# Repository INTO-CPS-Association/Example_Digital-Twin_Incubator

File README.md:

# Example Digital Twin: The Incubator

This is a case study of an Incubator with the purpose of understanding the steps and processes involved in developing a digital twin system.
This incubator is an insulated container with the ability to keep a temperature and heat, but not cool.

To understand what a digital twin is, we recommend you read/watch one or more of the following resources:
- Feng, Hao, Cláudio Gomes, Casper Thule, Kenneth Lausdahl, Alexandros Iosifidis, and Peter Gorm Larsen. “Introduction to Digital Twin Engineering.” In 2021 Annual Modeling and Simulation Conference (ANNSIM), 1–12. Fairfax, VA, USA: IEEE, 2021. https://doi.org/10.23919/ANNSIM52504.2021.9552135.
- [Claudio's presentation at Aarhus IT](https://videos.ida.dk/media/Introduction+to+Digital+Twin+Engineering+with+Cl%C3%A1udio+%C3%82ngelo+Gon%C3%A7alves+Gomes%2C+Aarhus+Universitet/1_7r1j05g8/256930613)

# Contents
- [Example Digital Twin: The Incubator](#example-digital-twin-the-incubator)
- [Contents](#contents)
- [About this Document](#about-this-document)
- [Overview of the Documentation](#overview-of-the-documentation)
   - [Searching](#searching)
- [Terminology](#terminology)
- [Our Concept of Digital Twin](#our-concept-of-digital-twin)
- [The Incubator Physical Twin](#the-incubator-physical-twin)
   - [Hardware Overview](#hardware-overview)
      - [Raspberry Pi GPIO connections](#raspberry-pi-gpio-connections)
      - [Temperature Sensor Mapping](#temperature-sensor-mapping)
      - [Connecting to the Raspberry PI](#connecting-to-the-raspberry-pi)
   - [CAD Model](#cad-model)
   - [Dynamic Models](#dynamic-models)
   - [Running The Incubator Physical Twin](#running-the-incubator-physical-twin)
- [The Digital Twin](#the-digital-twin)
   - [System Architecture](#system-architecture)
      - [Self-Adaptation](#self-adaptation)
   - [Datasets and Experiment Reports](#datasets-and-experiment-reports)
   - [Running the Digital Twin](#running-the-digital-twin)
      - [First-time Setup](#first-time-setup)
      - [After First-time Setup: Starting the DT Framework](#after-first-time-setup-starting-the-dt-framework)
      - [Running Unit Tests](#running-unit-tests)
      - [Running Integration Tests](#running-integration-tests)
- [Start visualization](#start-visualization)
- [Command Line Utilities to Interact with DT](#command-line-utilities-to-interact-with-dt)
   - [Mess With Lid Script](#mess-with-lid-script)
- [Diagnosing Startup Errors](#diagnosing-startup-errors)
   - [RabbitMQ Setup](#rabbitmq-setup)
   - [InfluxDB Setup](#influxdb-setup)
      - [First time configuration of InfluxDB server](#first-time-configuration-of-influxdb-server)
      - [Start InfluxDB server](#start-influxdb-server)
      - [Management of Influxdb](#management-of-influxdb)
      - [Initial Setup of Database](#initial-setup-of-database)
      - [Common Errors](#common-errors)
         - [Unauthorized API access](#unauthorized-api-access)
- [Repository Maintenance Instructions](#repository-maintenance-instructions)
   - [Code Organization](#code-organization)
# About this Document

**Goal:** The goal of this document is to provide users with a basic overview of the digital twin incubator and enabled them to run it on their computers.

**Audience:** This documentation is targeted at users who are acquainted with running programs from the command line and are able to install [python](https://www.python.org/) and run python scripts.

# Overview of the Documentation

The documentation is all contained into a single document for simplicity and ease of maintenance.
If the user wishes to see the documentation in some other format then we recommend cloning this repository and using [Pandoc](https://pandoc.org/) to convert the documentation into another format.

## Searching

Searching the documentation can be done by using the browser search function or using Github's search feature on top of the screen.

# Terminology

- **Plant** -- we use the term in the traditional control systems sense. The plant refers to the box contents, the heater, the sensor, and the fan. Basically it is the stuff that the controller is sensing and actuating on.
- **Controller** -- To control this responsibility is to decide when to turn on/off the heater.
- **Low Level Driver** --- This refers to the component that decouples the controller from the plant. It forms a layer that abstracts away from the details of how the actuators and sensors work and enables us to run the whole system locally on a computer without the need to connect to a real plant.

# Our Concept of Digital Twin

A digital twin is a software system that supports the operation of a cps (called the physical twin).
So the following documentation describes the physical twin first and then the digital twin.

# The Incubator Physical Twin

The overall purpose of the system is to reach a certain temperature within a box and keep the temperature regardless of content.

The system consists of:
- 1x Styrofoam box in order to have an insulated container
- 1x heat source to heat up the content within the Styrofoam box.
- 1x fan to distribute the heating within the box
- 2x temperature sensor to monitor the temperature within the box
- 1x temperature Sensor to monitor the temperature outside the box
- 1x controller to actuate the heat source and the fan and read sensory information from the temperature sensors, and communicate with the digital twin.

## Hardware Overview
Hardware Elements
- 3 temperature sensors of the type DS18S20
- 1 heat bed of the type RepRap PCB Heat bed MK2a (improved design)
  - Dimensions (Heat Bed): 200mm x 200mm
  - Resistance: 0.9 - 1.1 Ohms 
  - Operating voltage: 12 Volts
  - Operating current: 11 - 13 Amps
- 1 Fan 24V 92x25 B 87,4m³/h 34dBA - https://elektronik-lavpris.dk/files/sup2/EE92252B1-A99_D09023340G-00.pdf - https://elektronik-lavpris.dk/p122514/ee92252b1-a99-fan-24v-92x25-b-874m-h-34dba/
- Raspberry Pie starter kit
  - Raspberry Pi 4 Model B - 4 GB - https://www.raspberrypi.org/documentation/hardware/raspberrypi/bcm2711/rpi_DATA_2711_1p0_preliminary.pdf
  - 6GB Micro SD - Class A1 - Med NOOBS
  - Officiel Raspberry Pi USB-C Strømforsyning – EU – 5V 3A - Sort
  - Officiel Raspberry Pi 7" Touchscreen Display
  - SmartiPi Touch 2 - Case til Raspberry Pi 7" Touchscreen Display 
  - USB Micro SD Kortlæser
- Thermo box - Climapor thermokasse m/låg t/Eurokasse 54,5x35x18 cm
- Custom Printed Circuit Board Electronics. You can find more information [here](./software/docs/electronics/doc/doc.pdf).

### Raspberry Pi GPIO connections
- GPIO 12: PWM Heater 
- GPIO 13: PWM Fan
- GPIO 4: 1-wire temperature sensors

### Temperature Sensor Mapping
In order to read a temperature from the temperature sensors multiple IDs can be found in `/sys/bus/w1/devices/`.

If they are not visible there, check that the wires are well connected. Also check whether that the kernel submodules are active:
```bash
pi@incubatorpi:~/source/software $ lsmod | grep w1
w1_therm               28672  0
w1_gpio                16384  0
wire                   36864  2 w1_gpio,w1_therm
```

So to read a value from a sensor, one can do: `cat /sys/bus/w1/devices/10-0008039ad4ee/w1_slave`.

The sensors were connected according to [this online guide](https://www.circuitbasics.com/raspberry-pi-ds18b20-temperature-sensor-tutorial/).

Each ID in the `/sys/bus/w1/devices` folder correspond to a particular sensor. Follow the wires of the temperature sensors, and you will find a paper label with a number on it.
The ID to number mapping is:

ID to Sensor Number Mapping:

| ID              | Sensor Number |
|-----------------|:-------------:|
| 10-0008039ad4ee |       1       |
| 10-0008039b25c1 |       2       |
| 10-0008039a977a |       3       |

### Connecting to the Raspberry PI

The simplest is to just connect a keyboard, screen, and mouse to the pi, then use setup a hotspot with your phone, and connect the PI to it. Ensure that the rabbitmq server is accessible from the PI, and you should be able to run everything. We do not recommend running the influxdb within the PI itself. To gather data on the pi, we recommend [start_csv_data_recorder](software/startup/start_csv_data_recorder.py), which will store locally a set of csv files with the data from the [low_level_driver_server.py](software/incubator/physical_twin/low_level_driver_server.py). On another computer that has access to the rabbitmq server and influxdb server, you can run the [start_influx_data_recorder.py](software/startup/start_influx_data_recorder.py) to forward the data to the influxdb server.

You can SSH to the PI. The username and password is physically located on the Pi.

## CAD Model

A .obj file is available at: [figures/incubator_plant.obj](figures/incubator_plant.obj).

Ongoing development of the cad model is at 
[incubator](https://www.tinkercad.com/things/ls1YolyX1fc-incubatorv20230429)

## Dynamic Models

Most models are implemented using the [oomodellingpython](https://gitlab.au.dk/clagms/oomodellingpython/) package.

Models can be organized as plant models, [controller models](software/incubator/models/controller_models), or physical twin models (the later couple plant and controller together):
- Controller Models: we have implemented multiple controller models but only document the following:
  - [controller_model4](software/incubator/models/controller_models/controller_model4.py) -- This is like a [bang bang controller](https://en.wikipedia.org/wiki/Bang%E2%80%93bang_control) which tries to keep the temperature within an upper and lower bound.
- Plant Models: we have implemented multiple plant models but document the following:
  - [four_parameter_model](software/incubator/models/plant_models/four_parameters_model/four_parameter_model.py) --- this model represents the average temperature dynamics inside the box considering both the heater and the air as heat accumulating entities.
- [Physical Twin Models](software/incubator/models/physical_twin_models):
  -  [system_model4](software/incubator/models/physical_twin_models/system_model4.py) --- this model couples the controller_model4 model and the four_parameter_model.

## Running The Incubator Physical Twin

On the raspberry pi: 
1. Start the [low_level_driver_server.py](software/incubator/physical_twin/low_level_driver_server.py)
   ```powershell 
   PS software> python -m incubator.physical_twin.low_level_driver_server
   ```
2. Start the controller you wish to use. For example the [start_controller_physical.py](software/startup/start_controller_physical.py) is:
   ```powershell 
   PS software> python -m startup.start_controller_physical
   ```

# The Digital Twin

The DT follows a service based architecture, with different services communicating with each other via a [RabbitMQ message exchange](https://www.rabbitmq.com/) running on a [docker](https://www.docker.com/products/docker-desktop) container.
Each service is started with a python script, and most services refer to [software/startup.conf](software/startup.conf) for their configuration.

The code that starts the services is in [software/startup](software/startup).
It is possible to start all services (except the 3D visualization service) from the same script [software/startup/start_all_services.py](software/startup/start_all_services.py) or each service individually.

The services (and their starting scripts) currently implemented are:
- [incubator_realtime_mockup](software/startup/start_incubator_realtime_mockup.py) -- implements a real time plant simulation mockup so that the whole digital twin system can be run locally on any computer without the need to connect to an external physical twin. When using a real physical twin this service is not started.
- [low_level_driver_mockup](software/startup/start_low_level_driver_mockup.py) -- This instantiates a low level driver service that is wired to work with a real time plant simulator mockup. When using a real physical twin this service is not started.
- [influx_data_recorder](software/startup/start_influx_data_recorder.py) -- the service listens to a particular topic from RabbitMQ records the messages into the time series database [InfluxDB](https://portal.influxdata.com/downloads/)
- [plant_kalmanfilter](software/startup/start_plant_kalmanfilter.py) -- This service estimates the full state of the system and is used as a basis for anomaly detection.
- [plant_simulator](software/startup/start_plant_simulator.py) -- The service can run simulations based on the data from the time series database with different conditions for the plant model.
- [simulator](software/startup/start_simulator.py) -- This service can run simulations of the controller and plant system from data based on the data from the time series databases with different conditions.
- [calibrator](software/startup/start_calibrator.py) -- The service can use data from the time series database to estimate the parameters of the plant model.
- [controller_physical](software/startup/start_controller_physical.py) -- this service implements the controller.
- [supervisor](software/startup/start_supervisor.py) -- This service can periodically retune the controller.
- [self_adaptation_manager](software/startup/start_self_adaptation_manager.py) -- the service implements the self-adaptation which checks whether the physical characteristics of the plant have changed and can trigger a recalibration as well as controller tuning when that happens.
- [3d_visualization](software/digital_twin/visualization/project.godot) -- This service is a [Godot](https://godotengine.org/) project that shows a 3D rendering of the incubator. 
- [energy_saver](software/startup/start_energy_saver.py) -- This service is a simplified version of [self_adaptation_manager](software/startup/start_self_adaptation_manager.py) that reconfigures the controller to a lower energy consumption configuration when the lid is open.

## System Architecture

We use the [C4 Model](https://c4model.com/) to document the software architecture.

All communication goes through the RabbitMQ server, even the communication between the Controller and Plant.
The Controller communicates with the Plant by listening and sending RabbitMQ messages to the [low_level_driver_server.py](./software/incubator/physical_twin/low_level_driver_server.py).

Anyone else interested in this communication, such as the digital twin, can listen to it as well.

### Self-Adaptation

The most complex behavior is the self-adaptation, as it involves most implemented DT components.

This is introduced in the following paper, which we recommend you read:
- Feng, Hao, Cláudio Gomes, Santiago Gil, Peter H. Mikkelsen, Daniella Tola, Peter Gorm Larsen, and Michael Sandberg. “Integration Of The Mape-K Loop In Digital Twins.” In 2022 Annual Modeling and Simulation Conference (ANNSIM), 102–13. San Diego, CA, USA: IEEE, 2022. https://doi.org/10.23919/ANNSIM55834.2022.9859489.
- *Note that diagrams in the paper are likely outdated. Updated diagrams are shown below*

The main components and their dependencies are:

Legend:
- [MQ] - Communication happens via RabbitMQ messages.
- [API] - Communication happens via method call.

The following shows the main stages involved in a self-adaptation:

In particular, these are followed by the SelfAdaptationManager:

The following diagram shows the main interactions between the main entities that participate in the self-adaptation process. It is assumed that an anomaly has occurred due to the lid being open.

## Datasets and Experiment Reports

See [incubator/datasets](./software/incubator/datasets/README.md)

## Running the Digital Twin

It is possible to run the digital twin on our computer, with or without a connection to the physical twin.

*You're advised to read carefully all documentation before acting on any instruction.*

### First-time Setup
1. Open terminal in [software](software).
2. (Optional) Create a virtual environment: `python -m venv venv`
3. (Optional) Activate the virtual environment (there are multiple possible activate scripts. Pick the one for your terminal.): 
   1. Windows Powershell:`.\venv\Scripts\Activate.ps1` 
   2. Linux/Mac: `source venv/bin/activate`
4. (Optional) Install pip wheel: `pip install wheel`
5. Install dependencies:
   1. `pip install -r ./requirements.txt`
6. Install [docker](https://www.docker.com/products/docker-desktop) (see [Docker Homepage](https://docs.docker.com/desktop/))
   1. On Linux, also install the [Docker compose plugin](https://docs.docker.com/compose/install/linux/)
8. (Optional) Install [Godot](https://godotengine.org/) in case you want to load a 3D visualization. 

### After First-time Setup: Starting the DT Framework

1. Inspect the [startup.conf](./software/startup.conf) in this folder. You should not need to change anything for running the DT locally.
2. Make sure docker is running. 
3. Run
   ```bash
   software$ python -m startup.start_all_services
   ```
4. After starting all services successfully, the controller service will start producing output that looks like the following:
   ````
   time           execution_interval  elapsed  heater_on  fan_on   room   box_air_temperature  state 
   19/11 16:17:59  3.00                0.01     True       False   10.70  19.68                Heating
   19/11 16:18:02  3.00                0.03     True       True    10.70  19.57                Heating
   19/11 16:18:05  3.00                0.01     True       True    10.70  19.57                Heating
   19/11 16:18:08  3.00                0.01     True       True    10.69  19.47                Heating
   19/11 16:18:11  3.00                0.01     True       True    10.69  19.41                Heating
   ````
5. Login to http://localhost:8086/ (or more generally http://[Influxdb_IP]:8086/) to see the influxdb management page, were you can create dashboards to see the data produced by the incubator. The login details are:
   - user=`incubator`
   - password=`incubator`
6. Login http://localhost:15672/ to see the RabbitMQ management page. The login details are:
   - user=`incubator`
   - password=`incubator`
7. Optional: [Start visualization](#start-visualization)
8. See [Diagnosing Startup Errors](#diagnosing-startup-errors) in case you encounter problems
9. Recommended: [Run the unit tests](#running-unit-tests)
10. Recommended: [Run the integration tests](#running-integration-tests)

### Running Unit Tests

Make sure you can successfully [start the DT framework](#after-first-time-setup-starting-the-dt-framework)

To run the unit tests, open a terminal in [software](software), and
1. Activate virtual environment
2. If using powershell, run [./run_tests.ps1](./software/run_tests.ps1)
3. Otherwise:
   1. Set environment variable `CLIMODE = "ON"`
   2. Run tests: `python -m unittest discover -v incubator/tests -p "*.py"`

### Running Integration Tests

Make sure you can successfully [start the DT framework](#after-first-time-setup-starting-the-dt-framework) and [run the unit tests](#running-unit-tests) before attempting to run the integration tests.

The script [run_integration_tests.ps1](./software/run_integration_tests.ps1) contains the instructions.

# Start visualization

We assume the reader is broadly familiar with [Godot](https://godotengine.org/) engine.

1. Download and install [Godot Engine - .NET v4.1.1](https://godotengine.org/download/archive/4.1.1-stable/). 
   * Note that it must be the .NET version.
   * You may also need to install the [.NET SDK](https://dotnet.microsoft.com/en-us/download)
2. Open [project.godot](software/digital_twin/visualization/project.godot) with Godot engine.
3. The UI should look like:
   
4. Make sure the RabbitMQ server is running.
5. Build and run the project by clicking on the "play" button in the top-right corner (or press F5). 
   1. If the application crashes when opening the project, it could be due to:
      1. Connection from Godot to Rabbitmq server failed (check the Errors tab in Godot UI).
      2. You GPU does not support the Vulkan rendering API. Open a terminal and run the following command: 
      ```
      C:\path\to\your\godot4.exe --rendering-driver opengl3.
      ```
6. In the connection menu, add the connection configuration parameters that are in the [startup.conf](software/startup.conf). The result should look like this:
   
7. Press connect and then start. It will look like this:

# Command Line Utilities to Interact with DT
The Incubator contains several scripts for interacting with the DT as it is running live. The scripts can be found in [software/cli](software/cli).
The scripts can be executed by following the pattern: `python -m cli.<script_name>`.<br>
For instance, to generate dummy data the following script can be executed: `python -m cli.generate_dummy_data`. Notice that some scripts require extra parameters.

## Mess With Lid Script
Certain configurations of the Incubator support anomaly detection to determine if the styrofoam lid has been removed from the box.<br>
When running a mocked version of the PT, the behavior of removing the lid can be simulated through the [software/cli/mess_with_lid_mock.py](software/cli/mess_with_lid_mock.py) script.<br>
In practice, the simulation is accomplished by changing the $G_{box}$ parameter of the mocked PT. The $G_{box}$ represents the rate of energy transfer between the air inside the box and the air outside the box.

**Executing the script:**<br>
The script can be executed by running `python -m cli.mess_with_lid_mock <N>`, where $N$ represents a positive integer to multiply the original $G_{box}$ with.<br>
For instance, the `python -m cli.mess_with_lid_mock 100` simulates a greater loss of energy to the outside (lid off) and `python -m cli.mess_with_lid_mock 1` simulates the original behavior (lid on).

# Diagnosing Startup Errors

If any errors show up during the startup process, check that the RabbitMQ server and InfluxDB are being correctly started. 

The following instructions were used to configure these services in the first time and may help you test them:

## RabbitMQ Setup

To start the RabbitMQ server, run the following in [software/incubator/communication/installation](software/incubator/communication/installation):
``` Powershell
# start and install rabbitmq container
PS software\incubator\communication\installation> docker-compose up --detach --build
[MACOS: docker compose up --detach --build]

# Check logs of rabbitmq-server
PS software\incubator\communication\installation> docker logs rabbitmq-server

# Run script to test server (assumes you have correct environment)
cd [RepoRoot]\software\
[Activate virtual environment]
PS software> python -m incubator.communication.installation.test_server

# Stop and remove the server
PS software> docker-compose down -v
[MACOS: docker compose down -v]
```

The script should produce:
```
Sending message...
Message sent.
Retrieving message. Received message is {'text': '321'}
```

More information about the [Dockerfile](software/incubator/communication/installation/Dockerfile):
https://hub.docker.com/_/rabbitmq

Management of local RabbitMQ:
1. Start RabbitMQ server
2. Open http://localhost:15672/ on your browser.
3. User and pass configuration are stored in [rabbitmq.conf](software/incubator/communication/installation/rabbitmq.conf) and passed to the container through the [Dockerfile](software/incubator/communication/installation/Dockerfile)

## InfluxDB Setup

### First time configuration of InfluxDB server

Run the following if this is the first time you're starting the InfluxDB server:
1. Unzip [influxdb.zip](./software/digital_twin/data_access/influxdbserver/influxdb.zip) into a new directory called [influxdb](./software/digital_twin/data_access/influxdbserver/influxdb).
   The directory tree should look like: 
   ```powershell
   influxdb
   │   config.yaml
   │   docker-compose.yml
   │   Dockerfile
   │   influxdb.zip
   │   README.md
   │   test_server.py
   └── influxdb
       │   influxd.bolt
       └── engine
           │   data
           └── wal
   ```
2. This directory tree will contain all the data stored in InfluxDB, even if the virtual machine is deleted. So you can back it up if you want to protect the data.
3. [Start the InfluxDB server](#start-influxdb-server).

### Start InfluxDB server

To start the InfluxDB server, run from the [influxdbserver](software/digital_twin/data_access/influxdbserver) folder:
1. Start InfluxDB:
   ```Powershell
   PS software\digital_twin\data_access\influxdbserver> docker-compose up --detach --build
   ```
2. Run script to test connection to InfluxDB
   ```Powershell
   PS software\digital_twin\data_access\influxdbserver> cd [RepoRoot]\software
   [Activate virtual environment]
   PS software> python -m digital_twin.data_access.influxdbserver.test_server
   ```
3. See the data produced by the script by logging in to http://localhost:8086/ (user and password below) and opening the test dashboard.
4. Stop and remove the server:
   ```Powershell
   docker-compose down -v
   ```

More information: https://docs.influxdata.com/influxdb/v2.0/get-started/

### Management of Influxdb

1. Start InfluxDB server
2. Open http://localhost:8086/ on your browser.
3. Alternative, open a terminal in the container: `docker exec -it influxdb-server /bin/bash`

### Initial Setup of Database

This has been done once, and there's no need to repeat it.
But it is left here in case we lose the file [influxdb.zip](./software/digital_twin/data_access/influxdbserver/influxdb.zip).

1. Open http://localhost:8086/
2. Press Get-Started
3. Enter information:
    ```
    user: incubator
    pass: incubator
    organization: incubator
    bucket: incubator 
    ```
4. Run the [test_server.py](software/digital_twin/data_access/influxdbserver/test_server.py) script to start pushing random data onto the db.
5. Create dashboards by importing the json files in [dashboards](software/digital_twin/data_access/influxdbserver/dashboards) in the management page.

### Common Errors

#### Unauthorized API access

If while running `test_server` in [Start influxdb server](#start-influxdb-server), you get an error resembling the following:
```
> write_api.write(bucket, org, point)
(Pdb) config["influxdb"]
ConfigTree([('url', 'http://localhost:8086'), ('token', '-g7q1xIvZqY8BA82zC7uMmJS1zeTj61SQjDCY40DkY6IpPBpvna2YoQPdSeENiekgVLMd91xA95smSkhhbtO7Q=='), ('org', 'incubator'), ('bucket', 'incubator')])
influxdb_client.rest.ApiException: (401)
Reason: Unauthorized
HTTP response headers: HTTPHeaderDict({'Content-Type': 'application/json; charset=utf-8', 'X-Platform-Error-Code': 'unauthorized', 'Date': 'Wed, 31 Aug 2022 09:35:17 GMT', 'Content-Length': '55'})
HTTP response body: {"code":"unauthorized","message":"unauthorized access"}
-> write_api.write(bucket, org, point)
```

Then the cause is the token used in the [startup.conf](software/startup.conf) needs to be updated.
To fix open the InfluxDB web management page, go to InfluxDB->Tokens and generate a new token. Then update [startup.conf](software/startup.conf) with the new token.

Original issue described in [#23](https://github.com/INTO-CPS-Association/example_digital-twin_incubator/issues/23).

# Repository Maintenance Instructions

We make extensive use of README.md files. Please read them and keep them up to date.

General guidelines:
1. Run the tests as often as possible.
2. Create tests as much as possible. If the tests are long running, such as calibrations and optimizations, create a version of the test that runs faster (e.g., on a subset of data) when running the tests from the command line. See [example_test.py](./software/incubator/tests/example_test.py).
3. Create code that is testable.
4. Ask for code reviews (code readable by at least two people is more likely readable by a third)
5. Organize and document datasets and experiments.
6. Beware of large datasets. Host them elsewhere if needed, but include a short version of the dataset in the repository.
7. Don't be afraid of reorganizing the code and repo if you think that's necessary. This is an ongoing learning process for everyone. Discuss with Casper, Kenneth, or Claudio before doing so if you're not sure.
8. We shy away from branches except when they add a substantial amount of functionality. 
9. Commit and push responsibly to the main branch, that is, always make sure that:
   1. That all tests pass (unit tests and integration tests).
   2. That new code is documented and tested.
   3. That documentation links are not broken. 
      1. Use for example, [markdown-link-check](https://github.com/tcort/markdown-link-check) to check all md files for broken links:
         ```powershell
         Get-ChildItem -Include *.md -Recurse | Foreach {markdown-link-check --config .\markdown_link_check_config.json $_.fullname}
         ```
      2. If relevant, regenerate the [Table of Contents](#contents), either by hand or (recommended) using [Markdown All in One](https://marketplace.visualstudio.com/items?itemName=yzhang.markdown-all-in-one) or some other utility.
10. Much more on https://github.com/HugoMatilla/The-Pragmatic-Programmer

## Code Organization

The [software](software) directory contains all things code related.
- [cli](./software/cli) -- Contains code to communicate with the running DT components.
- [digital_twin](./software/digital_twin) -- Code that forms the digital twin services.
- [incubator](./software/incubator) -- Code that implements the physical twin, models, and datasets
- [integration_tests](./software/integration_tests) -- Code to run integration tests.
- [mock_plant](./software/mock_plant) -- Code setting up the local virtual incubator plant.
- [startup](./software/startup) -- Code to start and stop the DT services.

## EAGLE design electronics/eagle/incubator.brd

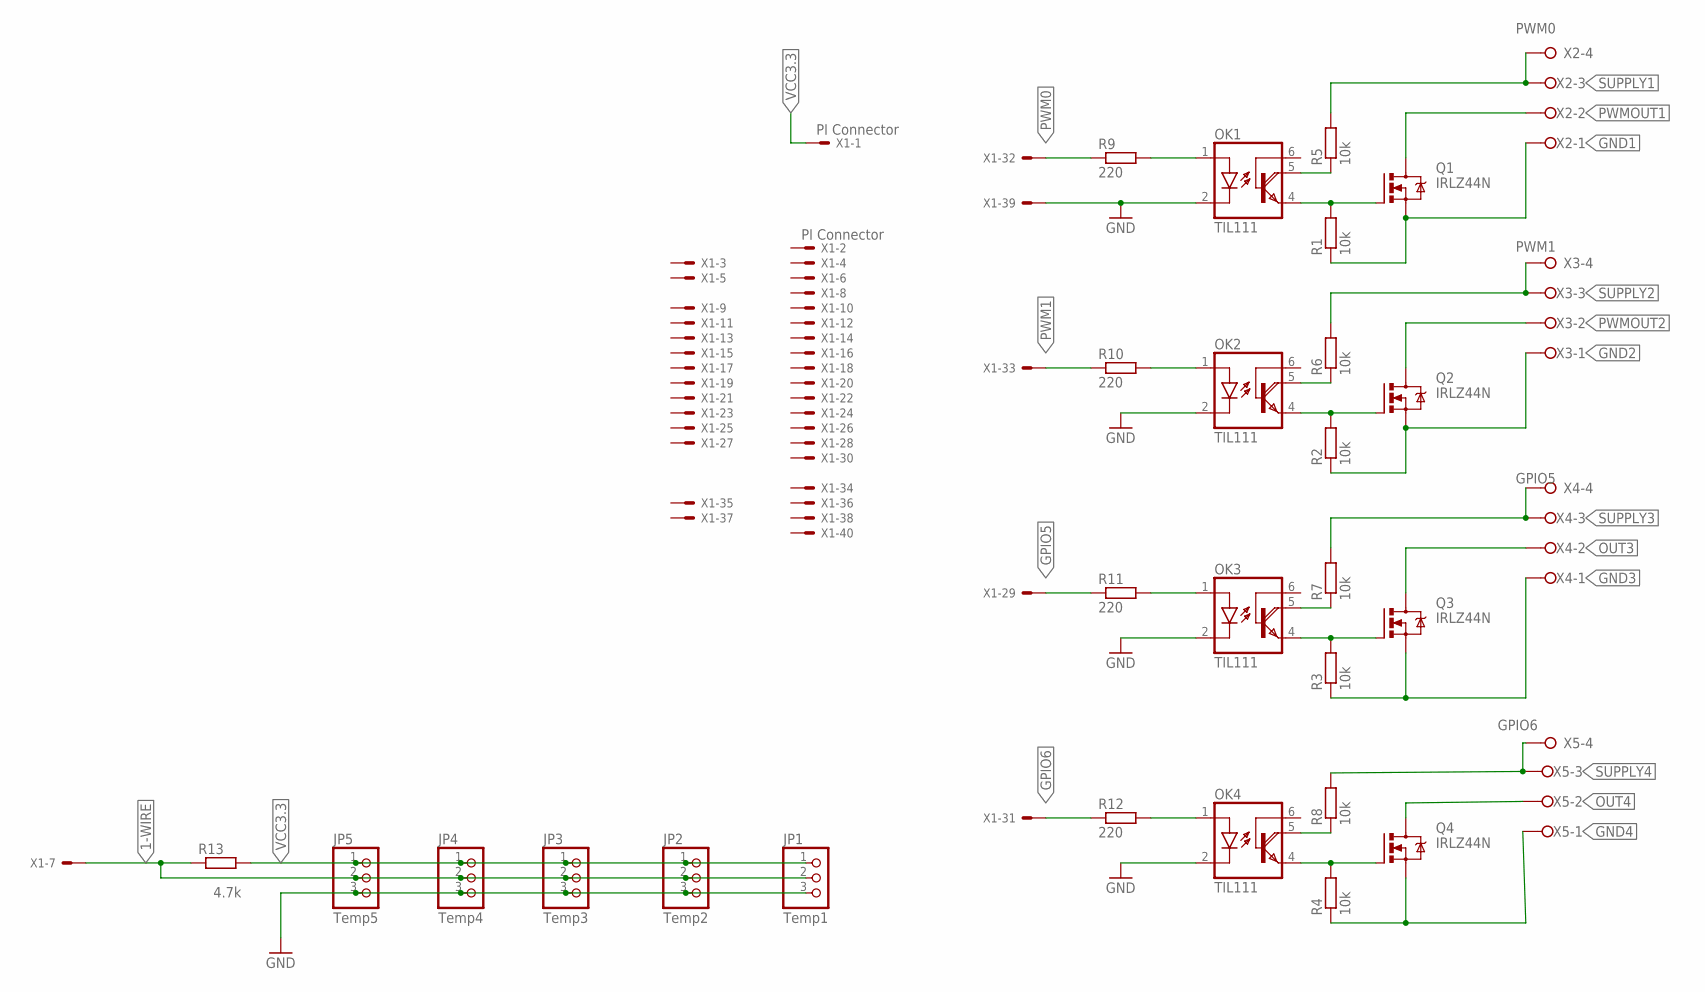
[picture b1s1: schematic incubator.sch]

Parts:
JP1: Temp1; 1X03
JP2: Temp2; 1X03
JP3: Temp3; 1X03
JP4: Temp4; 1X03
JP5: Temp5; 1X03
OK1, OK2, OK3, OK4: TIL111; DIL06
Q1, Q2, Q3, Q4: IRLZ44N; TO220BH
R1, R2, R3, R4, R5, R6, R7, R8: 10k; 0207/7
R9, R10, R11, R12: 220; 0207/7
R13: 4.7k; 0207/7
X1: PI Connector; 87758-4016
X2: PWM0; W237-4P
X3: PWM1; W237-4P
X4: GPIO5; W237-4P
X5: GPIO6; W237-4P

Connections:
1-WIRE: JP1.2, JP2.2, JP3.2, JP4.2, JP5.2, R13.1, X1.7
GND: JP1.3, JP2.3, JP3.3, JP4.3, JP5.3, OK1.2 (C), OK2.2 (C), OK3.2 (C), OK4.2 (C), X1.39
GND1: Q1.S, R1.1, X2.1
GND2: Q2.S, R2.1, X3.1
GND3: Q3.S, R3.1, X4.1
GND4: Q4.S, R4.1, X5.1
GPIO5: R11.1, X1.29
GPIO6: R12.1, X1.31
unnamed: OK1.5 (COL), R5.1
unnamed: OK1.4 (E), Q1.G, R1.2
unnamed: OK2.5 (COL), R6.1
unnamed: OK2.4 (E), Q2.G, R2.2
unnamed: OK3.4 (E), Q3.G, R3.2
unnamed: OK3.5 (COL), R7.1
unnamed: OK4.5 (COL), R8.1
unnamed: OK4.4 (E), Q4.G, R4.2
unnamed: OK1.1 (A), R9.2
unnamed: OK2.1 (A), R10.2
unnamed: OK3.1 (A), R11.2
unnamed: OK4.1 (A), R12.2
OUT3: Q3.D, X4.2
OUT4: Q4.D, X5.2
PWM0: R9.1, X1.32
PWM1: R10.1, X1.33
PWMOUT1: Q1.D, X2.2
PWMOUT2: Q2.D, X3.2
SUPPLY1: R5.2, X2.3, X2.4
SUPPLY2: R6.2, X3.3, X3.4
SUPPLY3: R7.2, X4.3, X4.4
SUPPLY4: R8.2, X5.3, X5.4
VCC3.3: JP1.1, JP2.1, JP3.1, JP4.1, JP5.1, R13.2, X1.1

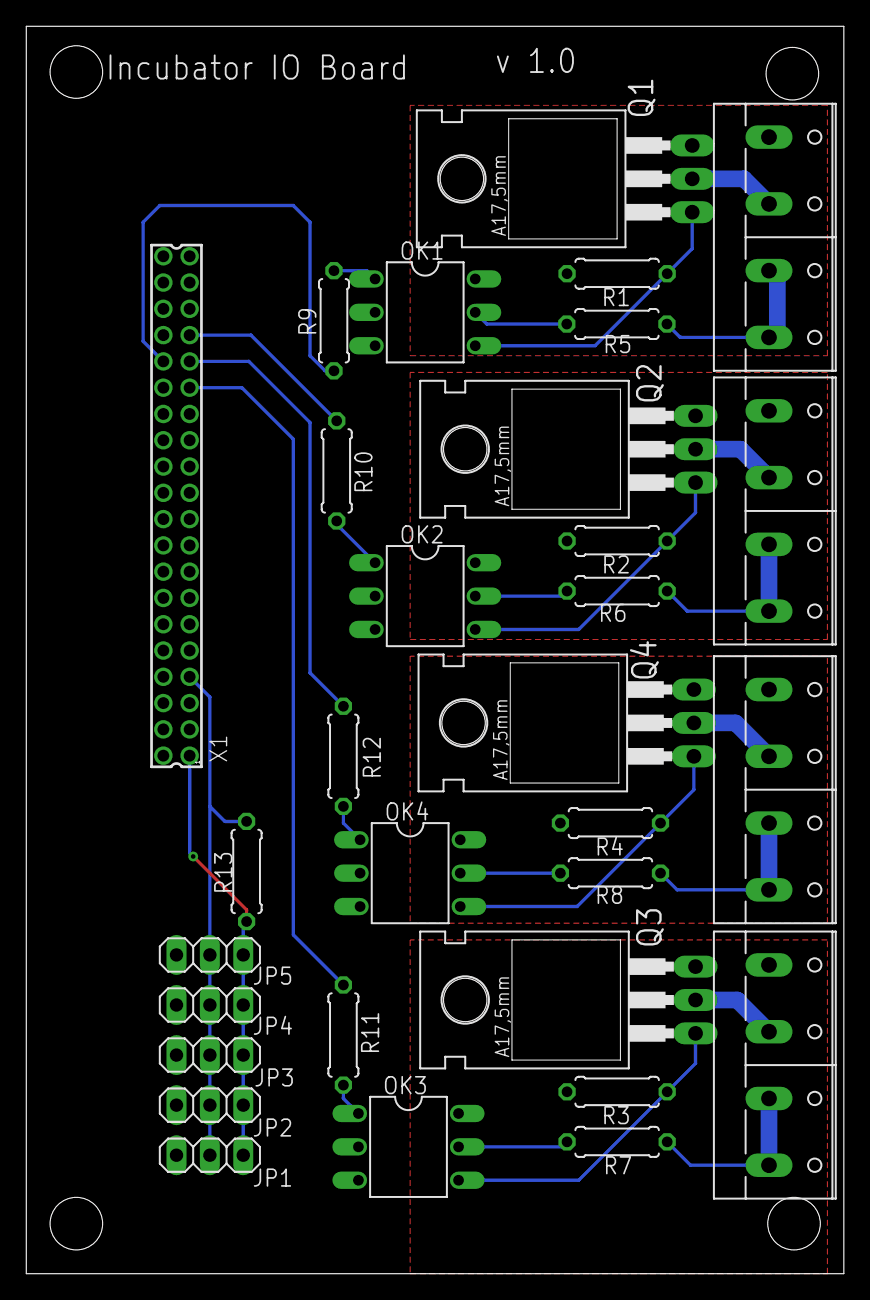
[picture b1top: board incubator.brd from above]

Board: 2 copper layers, 62.2 x 94.9 mm, 31 parts (0 on the bottom side), 31 nets.

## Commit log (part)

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2020-12-22 new calibration from new data.
2020-12-22 new files
2020-12-23 notes meeting with Kenneth
2020-12-23 rabbitmq server setup instructions
2020-12-23 removing old files no longer used.
2020-12-23 remove old files
2020-12-23 Refactor parameters for each model, for convenience. PArtial implementation of real time simulator.
2020-12-23 fix bug in low level driver
2020-12-23 remove commented out line
2020-12-23 Deleted a unused file
2020-12-24 prototype mockup physical twin improvements and code refactoring.
2020-12-24 remove unused files and refactor rabbitmq class parameter name
2020-12-24 remove ununsed code
2020-12-26 use rabbitmq class to subscribe to events.
2020-12-26 initial setup for database
2020-12-26 instructions and test script
2020-12-26 logging improved to try to find bug with abrupt socket termination
2020-12-26 basic data recording setup in place
2020-12-26 logging on controller and dashboard for influxdb
2020-12-27 make script independent of virtual env
2020-12-27 remove old software
2020-12-27 unify message format and generalize data recorder
2020-12-27 ste log level to default
2020-12-27 better dashboards/incubator_data.json
2020-12-27 revising queue names
2020-12-27 added content about how to install the Docker.
2020-12-28 moved diagrams to software folder
2020-12-28 refine seuqence diagrams
2020-12-28 Minor changes
2020-12-28 move files around, and decode json messages on callback of rabbitmqclass
2020-12-29 rpc server basic implementation for rabbitmq
2020-12-29 refactoring and implementation of basic RPC over rabbitmq.
2020-12-29 refactor echo method
2020-12-29 improvements to RPC server so that methods are validated properly.
2020-12-29 progress on simulator component
2020-12-29 basic what-if simulation with dummy historical data running
2020-12-29 example query to database
2020-12-30 generate dummy temp data
2020-12-31 plant simulator updated to return more compact set of results and not use db
2020-12-31 basic calibration done
2020-12-31 calibration running and recording to db.
2021-01-04 remove redundant test
2021-01-04 calibration is now run only for the parameters. This means it has to be run from a known initial heater temperature. Trying to guess the initial heater state causes the calibration process to fail of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
2021-01-04 Changes from meeting with Casper
2021-01-05 added starting docker python script
2021-01-08 refactor to allow for reply to messages before finishing the method.
2021-01-08 Added information on the inflxudb and rabbitmq python scripts
2021-01-08 add missing dependencies to requirements and code format
2021-01-08 Added configuration file, refactor to use config file, and script to start all services.
2021-01-08 remove old script, to avoid confusion
2021-01-09 better dashboard
2021-01-11 integration test checking f dumy data has been generated. Better db starting point, that includes the dashboard.
2021-01-13 Fixed issue with docker service starter
2021-01-13 removed pywin
2021-01-19 added meeting notes
2021-01-22 test for a error
2021-01-22 fixed the type issues on the sensor reading
2021-01-28 Add config file example
2021-01-28 Remove and ignore startup conf file.
2021-01-28 made csv data recorder record timestamp.
2021-01-28 Fix missing time column in dataset.
2021-01-28 plotting incubator events and model
2021-01-28 plotting kalman filter from the physical experiments.
2021-01-29 photos and description of experiment
2021-02-09 remove submodule
2021-02-09 Moved submodule
2021-02-10 reorganizing imports.
2021-02-10 Move DT keys into this repo.
2021-02-17 Created initial wireframe
2021-03-04 Set correct KF std dev.
2021-03-16 updated wireframe
2021-04-06 fixed boolean check
2021-04-19 added new experiment setup
2021-04-22 Updated submodule
2021-04-22 updated with results
2021-05-11 new meeting
2021-05-19 Update documentation.
2021-05-19 Reverted c7eb32f93ea467a7e09a8fb71b28e4d4c867f7ec . Tests passing now.
2021-05-25 Lid open server (work in progress).
2021-05-25 Refactor: query data aligned by timestamps from DB in a generic and safe way.
2021-05-26 Improvements to integration tests (not done yet).
2021-05-26 Integration tests extended to include more components. Several bugs fixed.
2021-07-08 added missing meeting
2021-07-09 add 0d models
2021-07-13 Fix failing script.
2021-07-13 test_server.py fix
2021-07-13 Fix config script.
2021-07-20 plot for mpm4cps paper.
2021-07-22 updated readme of main repo, and startup readme
2021-08-18 Add pause between generating and querying data.
2021-09-09 Update submodule.
2021-09-15 add instructions about the real experiments
2021-09-15 simplify requirements into a more optimistic approach: we constraint version when we found new problems.
2021-11-19 Typo
2022-02-28 Add new open loop controller.
2022-02-28 Note on issue.
2022-02-28 fixed typo
2022-03-01 Update plant parameters to match the ones from the latest experiment.
2022-03-01 WIP: self adaptation.
2022-03-03 WIP: setting up recalibration using kalman filter and dummy database.
2022-03-03 Test explicit recalibration.
2022-03-04 WIP: refactoring and scafolding of main interfaces.
2022-03-04 WIP: controller optimizer
2022-03-05 WIP: self_adaptation results (still unsafe)
2022-03-05 WIP: Display controller predicted trajectory
2022-03-05 Self-adaptation look completed.
2022-03-08 Cosmetic improvements.
2022-03-08 Fix bug in plant simulator server, introduced during the self adaptation loop coding.
2022-03-08 WIP: Integrate self-adaptation manager into framework
2022-03-10 Minimum prototype dt with self adaptation done.
2022-03-10 Fixing problems with room temperature and bug in instantiation of Kalman Filter.
2022-03-11 Finetuning Kalman Filter
2022-03-11 Parameters finetuned for simulation
2022-03-11 Avoid forcing docker image build every time services are started. PLEASE REBUILD docker images following instructions.
2022-03-11 Fix typo
2022-03-11 Improve output when DB data is inconsistent.
2022-03-14 add a dataset but I forget the details
2022-04-29 Isolate bug pointed out by Thomas.
2022-04-30 Update oomodelling and fix bug highlighted by Thomas.
2023-04-18 Add ssl support example
2023-04-19 Add reminder on env var.
2023-04-19 Mapping to new temp sensor config
2023-04-20 Disable auto restart in docker.
2023-04-20 Change default logging
2023-04-20 Import of content from https://github.com/INTO-CPS-Association/example-incubator
2023-04-21 Import incubator docs.
2023-04-21 Fix missing dependencies for documentation.
2023-04-21 Add link to generated documentation.
2023-04-21 Remove restriction deploy action.
2023-04-21 deploy: e8fa77b880a324178b6727e74f13ec26d8cf7053
2023-04-21 Remove github workflow. Will use simple readme files for documentation, to avoid brittleness.
2023-04-21 Polish documentation
2023-04-21 Remove outdated documentation and merge the rest into readme files.
2023-04-22 Comment out aws connection, as it's not the default one.
2023-04-22 Polishing documentation
2023-04-22 Remove need to include incubator in pythonpath. Affects almost all import statements.
2023-04-22 Add debug messages to better profile timings of drivedr.
2023-04-22 Add log messages to driver.
2023-04-22 Attempt at using concurrency to make driver faster in I/O
2023-04-22 Make controller more resilient to network drops.
2023-04-22 Fix bug in ll driver due to concurrency.
2023-04-22 Alwasy set fan false. Safest way.
2023-04-22 Fix controller missing method.
2023-04-22 Make csv data recorder more resilient to connection drops.
2023-04-23 Add new line at end of file
2023-04-23 Improve documentation of datasets, and start porting old datasets to fulfill the requirements.
2023-04-23 Better format file.
2023-04-23 Make datasets according to requirements.
2023-04-23 WIP: Make datasets according to requirements.
2023-04-23 Refactor: clean imports
2023-04-23 Document unauthorized token error
2023-04-24 Add more documentation
2023-04-24 Expose covariance parameters of Kalman filter
2023-04-26 Refactor controller model to reuse same state machine, and add shortcut to colling down.
2023-04-26 Make SM independent of modelling framework, and remove parameters from controller, as they are in the sm.
2023-04-26 Refactor: remove unused feature in plotting function.
2023-05-01 Add better logging to resilient services, so error timestamps are known.
2023-05-01 Improve startup process, according to Peter H.'s feedback.
2023-05-02 Fix bug in data processing that failed with a events.csv of 1 line only.
2023-05-02 Update systme configuration because of the 4 new holes.
2023-05-02 MacOS bugfix. subprocess.run fails to use more than one string argument. Changed to single string
2023-05-02 Attempt at making docker command work for both windows and mac.
2023-06-05 Improve cli script to control low level driver.
2023-06-05 Add new dataset with current measurements.
2023-06-05 Add calibration for new dataset of 4p model, and refactor codebase to avoid using global heater voltage and current.
2023-06-05 Refactoring and bug fixing.
2023-06-20 Add missing named param to incubator real time mockup
2023-06-22 WIP to reoganize documentation
2023-06-23 Include documentation on how to setup and start DT for the first time.
2023-06-23 Remove readme files that were merged to main readme.
2023-06-23 Remove setup of time series database.
2023-06-23 Close previous unclosed plot figures.
2023-06-23 Add a note on the differences between parameters of similar models.
2023-07-07 Refactor code to expose default parameter values as they hide implicit information.
2023-07-07 Add actuator effort counter to state machine.
2023-07-07 Add actuator effort counter to controller model.
2023-07-07 Add labels.
2023-07-09 Feature: initial commit of SE documentation for incubator
2023-07-19 Remove auto save fig.
2023-07-19 Refactor confusing name of function
2023-07-19 Fix bug in data plotting of events. Should use the location and not the iloc.
2023-07-19 Fix bgu in misalignment in plotting. Should be using sol
2023-07-19 Shows an example of full diagnosis that is not successful because the Kalman filters are not converging fast enough to the correct dynamics
2023-07-26 fix(TBM) : finished incomplete sentence
2023-08-05 Fix bug where the measurement function was being used from the discretized system. This is a minor box since after a few samples it would not have any effect On the performance of the common filter. 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
2023-08-05 Preliminary example of the signal processing needed to conclude that the lid is opened thanks to the reset signals from both Kalman filters.
2023-08-09 Feature(SRS) : First draft of SRS complete
2023-08-11 Add draft of concept of operations
2023-08-24 update results in dataset documentation.
2023-09-10 Update rabbitmq local server dockerfile. Previous one was no longer supported.
2023-10-11 Add visualization
2023-10-11 Remove unused imports and meshes
2023-11-22 Reorganize visualization service and update documentation.
2023-11-22 Simplify camera, remove ability to change camera view. Update documentation with better screenshot.
2023-11-30 Add energy saver service.
2023-11-30 Adjust threshold
2023-11-30 Adjust prediction threshold
2023-12-07 Add entry point for energy saver service, and documentation.
2024-01-26 Improve plotting
2024-02-10 Documentation and add example connection menu.
2024-02-11 Change URI field to HostName and remove prefix
2024-02-11 Update connection
2024-03-08 Improved mess with lid script
2024-03-14 Changed RabbitMQ log level for certain messages
2024-03-14 Formatting for readability
2024-03-14 Emulates -> simulates
2024-04-05 WIP: plotting of decision support example for DT book.
2024-04-16 Add test showing decision support for power supply interrupt
2024-04-16 Fix typo in documentation
2024-04-22 Fixed typo in README
2024-05-27 Fix https://github.com/INTO-CPS-Association/example_digital-twin_incubator/issues/44
2024-10-02 Remove deprecated trapz method.
2024-10-03 Fix broken interface of the PT and plant simulators. Change the query to introduce pivot.
2024-10-18 Remove obsolute version attribute from docker compose.
2024-10-18 Refactor RPC server to be a child of RabbitMQ class.
2024-11-07 Add new dataset and calibration results. But first need to get this branch up to date, as I've fixed a number of issues in the meantime.
2024-11-07 param changes
2024-11-07 save fig.
2025-01-21 Add clarifications about Docker and Godot
    * Add link to docker compose plugin installation
    * Add link to .NET SDK for visualization
    * Clarify Godot details
2025-03-10 Low level driver can read from humidity and co2 sensors, and actuate the air pump
2025-03-17 Fixed simple typo
2025-05-12 Config updates
